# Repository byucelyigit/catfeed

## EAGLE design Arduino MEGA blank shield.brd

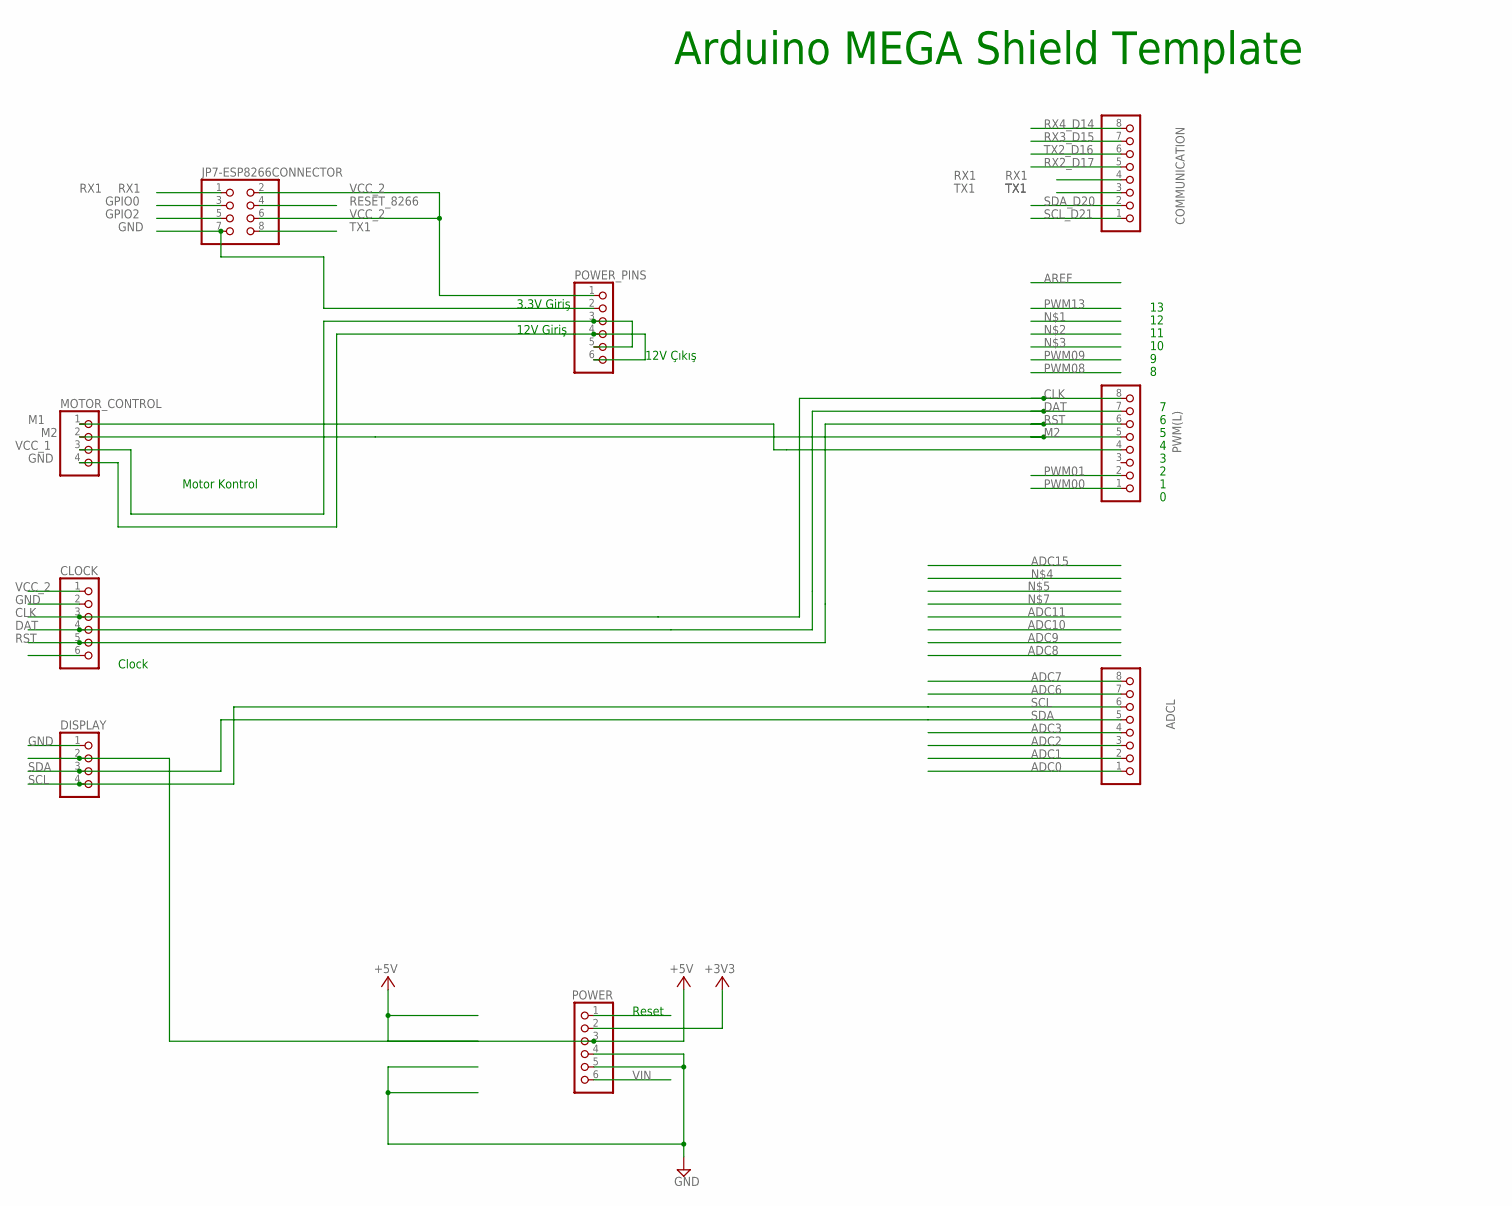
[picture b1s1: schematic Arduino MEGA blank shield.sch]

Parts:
ADCL: PINHD-1X8; 1X08
CLOCK: PINHD-1X6; 1X06
COMMUNICATION: PINHD-1X8; 1X08
DISPLAY: PINHD-1X4; 1X04
JP7-ESP8266CONNECTOR: PINHD-2X4; 2X04
MOTOR_CONTROL: PINHD-1X4; 1X04
POWER: PINHD-1X6; 1X06
POWER_PINS: PINHD-1X6; 1X06
PWM(L): PINHD-1X8; 1X08

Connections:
+3V3: POWER.2
+5V: DISPLAY.2, POWER.3
ADC0: ADCL.1
ADC1: ADCL.2
ADC2: ADCL.3
ADC3: ADCL.4
ADC6: ADCL.7
ADC7: ADCL.8
CLK: CLOCK.3, PWM(L).8
DAT: CLOCK.4, PWM(L).7
GND: CLOCK.2, DISPLAY.1, JP7-ESP8266CONNECTOR.7, MOTOR_CONTROL.4 (GND), POWER.4, POWER.5, POWER_PINS.2, POWER_PINS.4, POWER_PINS.6
GPIO0: JP7-ESP8266CONNECTOR.3
GPIO2: JP7-ESP8266CONNECTOR.5
M1: MOTOR_CONTROL.1, PWM(L).4
M2: MOTOR_CONTROL.2, PWM(L).5
PWM00: PWM(L).1
PWM01: PWM(L).2
RESET: POWER.1
RESET_8266: JP7-ESP8266CONNECTOR.4
RST: CLOCK.5, PWM(L).6
RX1: COMMUNICATION.4, JP7-ESP8266CONNECTOR.1
RX2_D17: COMMUNICATION.5
RX3_D15: COMMUNICATION.7
RX4_D14: COMMUNICATION.8
SCL: ADCL.6, DISPLAY.4 (GND)
SCL_D21: COMMUNICATION.1
SDA: ADCL.5, DISPLAY.3
SDA_D20: COMMUNICATION.2
TX1: COMMUNICATION.3, JP7-ESP8266CONNECTOR.8
TX2_D16: COMMUNICATION.6
VCC_1: MOTOR_CONTROL.3, POWER_PINS.3, POWER_PINS.5
VCC_2: CLOCK.1, JP7-ESP8266CONNECTOR.2, JP7-ESP8266CONNECTOR.6, POWER_PINS.1
VIN: POWER.6

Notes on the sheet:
Arduino MEGA Shield Template
Reset
Motor Kontrol
12V Giriş
12V Çıkış
Clock
3.3V Giriş

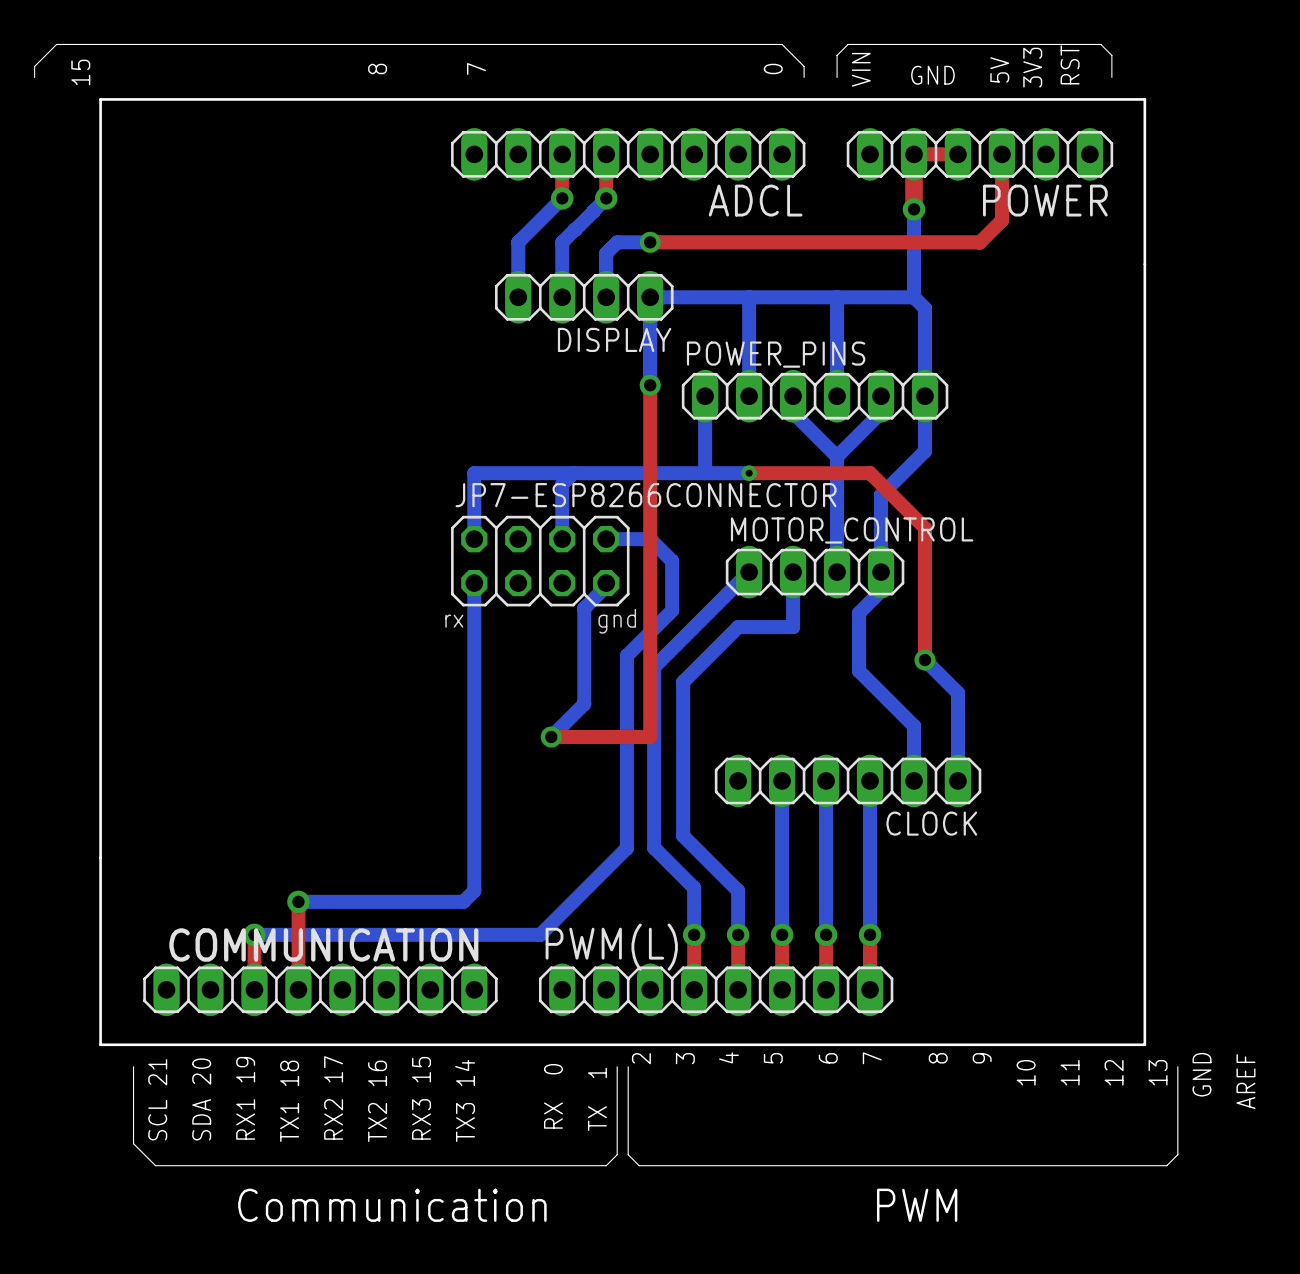
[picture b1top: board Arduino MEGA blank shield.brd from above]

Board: 2 copper layers, 70.9 x 69.4 mm, 9 parts (0 on the bottom side), 13 nets.

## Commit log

2019-01-25 test
2019-01-25 Project web page added as index.html
2019-01-25 byucelyigit
2019-01-25 https gerekti
2019-06-30 Alarm time information shows correct digits. repeat count increaed to 50
2019-06-30 motor start and stop added
2019-07-02 İki adet alarm değişikliğine başlandı.
    Test edilmedi. İkinci alarm set edecek komut numarası belirlenmedi. html değişikliği yapılmadı
